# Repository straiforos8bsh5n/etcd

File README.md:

# Ch55xduino: Small Devices Arduino for ch55x devices

**Getting started on the Ch55x the easy way. Forked from Sduino project, also based on 
ch554_sdcc project**

Ch55xduino is an Arduino-like programming API for the CH55X, a family of low-cost MCS51 USB MCU. The project tries to remove the difficulty of setting up a compiling environment. Users can simply write code in Arduino IDE and hit one button to flash the chip to get code running. No configuration or guesswork needed. 

CH551, CH552, CH554, may be the lowest part count system that works with Arduino. The minimal system only requires one chip, 2 decoupling capacitors, and one optional pull-up resistor. These features made it ideal for DIY projects. 

At this moment the project is still working-in-progress. Support most Arduino functions (Except pulse, shift, tone). Refer to examples in this repo for more info.

## Installation

Automatic IDE integration is supported via the
Arduino Boards Manager. This is the recommanded way of installation now. 

Start the Arduino-IDE. In *File->Preferences*, *Settings* tab, enter

> https://raw.githubusercontent.com/DeqingSun/ch55xduino/ch55xduino/package_ch55xduino_mcs51_index.json

as an *Additional Boards Manager URL*.

* Open *Tools->Board:...->Boards Manager*
* Find Ch55xduino by typing 'ch' into the search line
* Click on the list entry
* Click on *Install*.

Now you should find a new entry *CH55x Boards* in the list at
*Tools->Board:...*

* Choose *CH552 Board* from the list
* open the standard Blink example from *File->Examples->01. Basics->Blink*
* Change pin number in Blink example. For example, if you have LED on P3_0, you will write pin 30.
* compile it by hitting *Verify*
* If your board is never used with ch55xduino before, you need to make the ch55x chip enter bootloader mode. You need to disconnect USB and unpower ch55x, connect the pull-up resistor on D+ line (generally a 10K resistor between D+ and 5V, controlled by a push-button or adjacent pads). Then you connect USB. and hit *Upload*. Also, a blank new chip will enter the bootloader automatically.
* If you have used ch55xduino once and your code doesn't crash the USB subsystem, you can simply press *Upload*. Arduino and the firmware will kick the chip into the bootloader automatically.

### Installation without Github access

If you can not access github directly, use this link to a proxy instead.

> https://gh-proxy.deqing.workers.dev/raw.githubusercontent.com/DeqingSun/ch55xduino/playground/mirror/package_ch55xduino_mcs51_proxy_index.json

### USB and Serial upload

Ch55xduino supports both USB and Serial upload methods. If the USB port of the CH55x chip is connected to a host computer, the USB method is recommended.

It is also possible to upload via serial on UART1 of CH55x chips (except CH551). To set CH55x into bootloader mode automatically, you can connect RTS or DTR of a serial adaptor to an interrupt pin of CH55x with a capacitor, and add bootloader jumping code in the interrupt handler.

If you want to leave the bootloader, you may send the following bytes at 57600 baud. ```57 AB A2 01 00 01 A4```  

### Driver for windows

Since 0.0.10, if your Windows automatically installed the driver from wch.cn for the bootloader (4348,55E0), that is fine. The current upload tool can use the default CH375 driver and co-exist with the official [WCHISPTool](http://www.wch.cn/downloads/WCHISPTool_Setup_exe.html).

If you need to use WinUSB or libusb-win32, the tool will still work.

You can use USB Serial (CDC) driver for the default CDC USB stack (1209,C550). Use [Zadig](https://zadig.akeo.ie/) to install the driver if it did not install automatically.

If you tried to emulate another type of USB device without changing the PID/VID, you may need to uninstall the device before installing a new driver.

### Permission for Linux

By default, Linux will not expose enough permission for Arduino to upload the code with the USB bootloader. Copy ```99-ch55xbl.rules``` in this repo to ```/etc/udev/rules.d/``` and restart your computer. Otherwise, the upload tool may not find the bootloader device.

## Reference board

There is a small CH552 breakout board design in the "pcb" folder. When fabricated with 1.6mm board thickness, some USB receptacle may be too loose for the PCB. Just add some tape behind the USB connector to increase the thickness.

The button footprint was designed for 6mm buttons, but 5mm one works too.

## Difference to regular Arduino

### Pin names:

Regular Arduino uses continuous numbers to code pins on AVR chips. In my opinion, it makes more sense since AVR uses letters as a port name. But MCS51 core uses numbers as port names. So CH55xduino's pins using the following rule. 

```PortNumber*10+PinNumber```

For example, P1.1 is 11, P3.2 is 32.

### Analog input:

CH552 has an 8-bit, 4 channel analog-to-digital converter on pin P1.1, P1.4, P1.5, and P3.2. So the input range is 0~255, not 1023.

By default, all pins on the MCS51 microcontrollers have internal pull-up resistors enabled. You may need to use ```pinMode``` to set the pin to ```INPUT``` to disable the pull-up resistor. 

There is no Analog Pin definition such as A0. Just use 11, 14, 15, or 32 for their analog input feature.

### No polymorph functions:

There is no free C++ compiler for MCS51 chip, we can not use polymorph functions. However, since commit 13402 of SDCC, the generic selection is functional. Ch55xduino supports generic selection since 0.0.11.

If you are using a version higher than 0.0.11, the print function can choose a function according to the parameter's type. 

For example. If you want to print to the USB-CDC virtual serial port, you can do:

```
USBSerial_print(val);	//val: the value to print - any data type
USBSerial_print(val, format)	//specifies the number base (for integral data types) or number of decimal places (for floating point types)
USBSerial_print(charPointer, length)	//specifies the string length to be printed 
```

It is also possible to do ``` USBSerial_println ```. If you want to print to Serial0 or Serial1, just use ``` Serial0_print ``` or ``` Serial1_print ```.

Please note if you pass a character in single quotes, such as ```USBSerial_print(',');```, you will get ```44```. Because that char got promoted to integer type. You need to either use ```USBSerial_print((char)',');``` or ```USBSerial_print(",");```.

They are defined in ```genericPrintSelection.h```.

### Memory model:

Unlike most modern architectures including AVR, MCS51 has 2 RAM regions, internal data memory, and external data memory. For CH552, the internal one is only 256 bytes, and the external one is 1024 bytes.

CH55xduino uses the default Small Model for SDCC memory models. The small memory model will allocate all variables in internal, directly addressable RAM by default. Variables stored in external RAM must be declared with the ```xdata``` or ```far``` keyword. 

CH55xduino also put the stack in internal RAM. So there isn't much space left for variables. If your variable doesn't need fast access, use ```__xdata``` when you declare it.  

For example, if you are trying to allocate a lot of space in internal RAM.

```uint8_t testArr[128];```

You will trigger an error. ```?ASlink-Error-Could not get 130 consecutive bytes in internal RAM for area DSEG.``` This can be avoided by using

```__xdata uint8_t testArr[128];```

For the default Arduino setting, 148 bytes are reserved for USB endpoints. There will be 876 bytes usable for external RAM.

You can see the memory mapping by opening the map and mem file generated along with the hex file.

#### Common Pitfalls when Using SDCC

Note that when some function is called from an interrupt service routine it should be preceded by a #pragma NOOVERLAY (if it is not reentrant) . A special note here, int (16 bit) and long (32 bit) integer division, multiplication & modulus operations are implemented using external support routines developed in ANSI-C, if an interrupt service routine needs to do any of these operations then the support routines (as mentioned in a following section) will have to recompiled using the --stack-auto option and the source file will need to be compiled using the --int-long-rent compiler option. [src](http://fivedots.coe.psu.ac.th/~cj/masd/resources/sdcc-doc/SDCCUdoc-11.html)

With SDCC, interrupt service routine function prototypes must be placed in the file that contains main ( ) in order for an vector for the interrupt to be placed in the the interrupt vector space.  It's acceptable to place the function prototype in a header file as long as the header file is included in the file that contains main ( ).  SDCC will not generate any warnings or errors if this is not done, but the vector will not be in place so the ISR will not be executed when the interrupt occurs. [src](https://www.silabs.com/community/mcu/8-bit/knowledge-base.entry.html/2007/11/16/common_pitfalls_when-E7zi)

### Reset Pins

Unlike AVR chips, CH55x will reset when the RST pin is High. The reset pin may be configured as an input pin. But such configuration requires modification of Configuration Information byte, which require an external tool to do so.

## Known issues

.

## Included libraries

Most parts of the Arduino core system and some Arduino libraries are already ported to C-syntax. The resulting API is still very close to the C++ version and porting an existing application is not hard. Refer to the examples that come with the libraries.

#### Communication

* SPI: Real hardware-SPI up to 12MHz.

* SoftI2C: Bit-Bang I2C on any 2 pins.

* WS2812: Bit-Bang WS2812 on any pin. Note some compatible LEDs have different timing and some tweak may be needed. 

#### Sensors

* TouchKey: Internal 6-channel capacitive touch module wrapper with an adaptive baseline algorithm.

## Compatibility with the Arduino world

Since there is no free C++ compiler for the MCS51, it is impossible to do a
full 1:1 port of the whole enviroment as is has been done for the STM32 and
the ESP8266.

This is not a drop-in replacement for an AVR, but thanks to some C
preprocessor magic the programming API is still very, very similar and it is
often enough to just move over the opening bracket of the class
instanciation statement and to replace the dot in a method call for an
underscore. Check the [migration
guide](https://tenbaht.github.io/sduino/api/migration/) for an overview.

## Supported Systems:

Arduino IDE versions 1.8.12 are tested, but
most versions >=1.6.6 should work.

* Windows: Tested on Windows 7 and XP.

* MacOS: Tested on 10.14.

* Linux: Tested on Ubuntu 20.04 LTS.

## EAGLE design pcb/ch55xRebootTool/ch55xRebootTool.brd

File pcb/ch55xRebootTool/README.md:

# ch55xRebootTool

ch55xRebootTool is a hardware tool to reset a WCH chip target into the bootloader without touching the board with your finger. It solves 2 problems: 

1. Some chips can not jump to bootloader from user code.

2. When you are developing the USB host code, the USB port will be occupied by a device.

## How to use the tool

### Basic usage

Connect 2 micro USB cables from the computer to the 2 micro USB ports on the left. The upper one is connected to the target, and the lower one is to send commands to the controller on board.

The left MicroUSB port and the USB A port next to it are connected. The target can be plugged into either port.

If your target chip needs to pull down a pin to enter the bootloader, connect that pin to the P1.6 on the board. If the target uses D+, no connection is needed.

Open the ch55xRebootTool serial port @ 1200 rate and it will kick target into the bootloader.

### Use the serial adapter

This board can also be used as a serial adapter. Just use the 3-pin header on the right. Note the board can not work at the 1200 rate or higher than 115200. 

### Use a USB device for host code development

Plug the device on the USB port on the right side of the top. When the P1.7 on the board gets pulled down. The board will supply power to the device, and switch the target from the computer to the device. You may use a pin on the target to do the control

Note the target will switch back to the computer in bootloader mode.

## Enter the bootloader

Most WCH chips can upload firmware via USB. However, the chip must enter the bootloader to upload the firmware. Generally, there are 2 ways to enter bootloader:

1. Pull a specific pin to GND or D+ to VCC, depending on your settings in the configuration byte. Then power the chip.

2. Jump into the bootloader within the user code. But this does not work for chips such as CH549.

If you already played with the CH55xduino on a CH55x chip, you may not feel the pain. Because when you upload the code, the Arduino environment will open the virtual serial port on the CH55x chip at a 1200 baud rate. The CH55xduino firmware will jump to the bootloader automatically and receive the code from the computer. The user experience is just pressing a button on your computer and everything gets ready. 

But if the firmware is not working properly or you are using chips like CH549, the chip won't enter the bootloader automatically. You may need to unplug the USB cable, hold a button and plug the USB cable back, that is a pain when you repeat the process over and over again.

Instead of doing it manually, the ch55xRebootTool will act as a serial adapter. When you open the serial port at a 1200 baud rate, the tool will disconnect the power from the target chip using a PMOS, connect a 10K resistor to D+, and pulldown the pin P1.6, before restoring the power cycle. Basically, the ch55xRebootTool does the power cycle and pulls the pin for you. 

## Use a USB device

When developing the host code, you may need to switch the target back and forth between the computer and the device. This tool does it automatically for you. You just need to pull the Pin 1.7 low to connect the device. When it is released, the target will be connected back to the computer. 

When I design the board. I wish the target can send a reset command on the USB bus, and the controller knows when the target left the bootloader, and can switch to the device automatically. But I have not got it working so far.

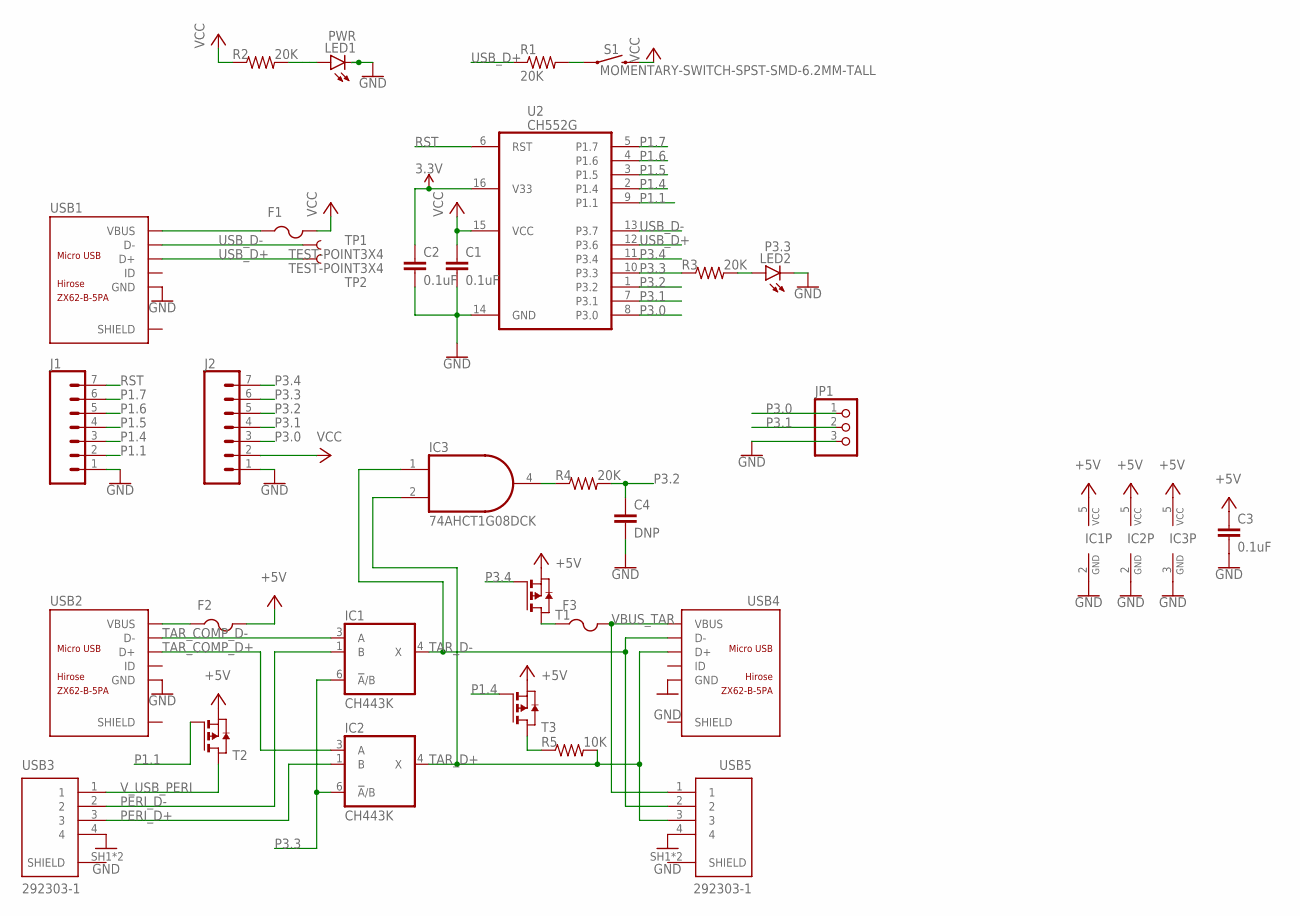
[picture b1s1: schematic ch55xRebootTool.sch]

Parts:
C1, C2, C3: 0.1uF; C0805K; LCSC C16834
C4: DNP; C0805K
F1, F2, F3: PTCFUSE-1206; R1206; LCSC C151162
IC1, IC2: CH443K; DCK_R-PDSO-G6; LCSC C125185
IC3: 74AHCT1G08DCK; SC70-5; LCSC C12493
J1, J2: CONN_07NO_SILK; 1X07_NO_SILK
JP1: PINHD-1X3; 1X03
LED1: PWR; GHI-BASICCOMPONENTS_0805-LED
LED2: P3.3; GHI-BASICCOMPONENTS_0805-LED
R1, R2, R3, R4: 20K; R0805
R5: 10K; R0805
S1: MOMENTARY-SWITCH-SPST-SMD-6.2MM-TALL; TACTILE_SWITCH_SMD_6.2MM_TALL
T1, T2, T3: PMOSSOT23; SOT-23
TP1, TP2: TEST-POINT3X4; PAD.03X.04
U2: CH552G; MY_IC_SO16; LCSC C111292
USB1, USB2, USB4: ZX62-B-5PA; MICRO-USB5+6P-SMD-0.65-AB; LCSC C10418
USB3, USB5: 292303-1; LCSC C2345

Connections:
3.3V: C2.1, U2.16 (V33)
+5V: C3.1, F2.2, IC1.5 (VCC), IC2.5 (VCC), IC3.5 (VCC), T1.2 (S), T2.2 (S), T3.2 (S)
GND: C1.2, C2.2, C3.2, C4.2, IC1.2 (GND), IC2.2 (GND), IC3.3 (GND), J1.1, J2.1, JP1.3, LED1.K, LED2.K, U2.14 (GND), USB1.5 (GND), USB2.5 (GND), USB3.4, USB4.5 (GND), USB5.4
unnamed: R1.2, S1.A2 (1)
unnamed: LED2.A, R3.2
unnamed: LED1.A, R2.2
unnamed: IC3.4 (O), R4.1
unnamed: F3.1, T1.1 (D)
unnamed: R5.1, T3.1 (D)
P1.1: J1.2, T2.3 (G), U2.9 (P1.1)
P1.4: J1.3, T3.3 (G), U2.2 (P1.4)
P1.5: J1.4, U2.3 (P1.5)
P1.6: J1.5, U2.4 (P1.6)
P1.7: J1.6, U2.5 (P1.7)
P3.0: J2.3, JP1.1, U2.8 (P3.0)
P3.1: J2.4, JP1.2, U2.7 (P3.1)
P3.2: C4.1, J2.5, R4.2, U2.1 (P3.2)
P3.3: IC1.6 (!A!/B), IC2.6 (!A!/B), J2.6, R3.1, U2.10 (P3.3)
P3.4: J2.7, T1.3 (G), U2.11 (P3.4)
PERI_D+: IC2.1 (B), USB3.3
PERI_D-: IC1.1 (B), USB3.2
RST: J1.7, U2.6 (RST)
SHIELD: USB3.SH1 (SHIELD), USB3.SH2 (SHIELD), USB5.SH1 (SHIELD), USB5.SH2 (SHIELD)
TAR_COMP_D+: IC2.3 (A), USB2.3 (D+)
TAR_COMP_D-: IC1.3 (A), USB2.2 (D-)
TAR_D+: IC2.4 (X), IC3.2 (I1), R5.2, USB4.3 (D+), USB5.3
TAR_D-: IC1.4 (X), IC3.1 (I0), USB4.2 (D-), USB5.2
USB_D+: R1.1, TP2.P$1, U2.12 (P3.6), USB1.3 (D+)
USB_D-: TP1.P$1, U2.13 (P3.7), USB1.2 (D-)
VBUS: F1.1, USB1.1 (VBUS)
VBUS_COMP: F2.1, USB2.1 (VBUS)
VBUS_TAR: F3.2, USB4.1 (VBUS), USB5.1
VCC: C1.1, F1.2, J2.2, R2.1, S1.B2 (2), U2.15 (VCC)
V_USB_PERI: T2.1 (D), USB3.1

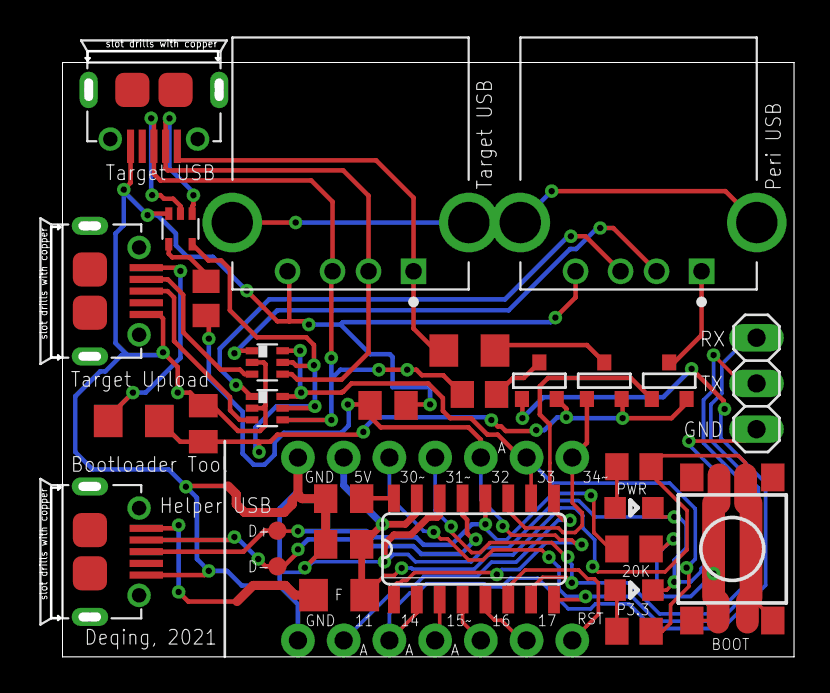
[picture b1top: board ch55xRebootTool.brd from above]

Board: 2 copper layers, 41.3 x 33.7 mm, 32 parts (0 on the bottom side), 34 nets.

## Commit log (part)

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2024-06-06 inital commit
2024-06-15 Implemented SWIM and CLI interface
2024-06-17 readme changed
2024-06-26 Multiple programmers are now supported
2024-07-05 Added parts DB
2024-07-13 Moved out_usleep to struct programmer_s
2024-07-23 Moved out_msg_size to struct programmer_s
2024-07-29 Detach device from kernel module
2024-08-05 test_unit_ready & related utility functions
2024-08-16 Use little-endian for data length
2024-08-22 Implemented stlinkv1 open
2024-08-25 Test stlinkv1 for being initialized
2024-08-26 Fixed stack smashing
2024-09-01 Implemented stlink_swim_read_range
2024-09-03 Implemented stlink_init_io
2024-09-15 Implemented stlink_prepare_transfer
2024-09-25 Got rid from segmentation fault when -b > 16
2024-09-29 Implemented stlink_swim_write_range
2024-10-03 Handle writing buffer overflow
2024-10-12 Limit write tries
2024-10-23 Implemented stlink_finish_session
2024-10-26 No need to write in DM_CSR2
2024-10-28 Implemented a block reading cycle
2024-10-31 Wrapped debug in DEBUG_PRINT(..)
2024-11-04 Fixed memory sizes
2024-11-11 Implemented stlink_swim_write_block
2024-11-16 Implemented stlink_swim_wait
2024-11-17 stlink_swim_get_status now respects the previous CBW
2024-11-22 Implemented writing by 128-byte blocks
2024-11-23 Padding blocks with '\0'
2024-12-03 Added make install
2024-12-04 Reset MCU core after writing completes
2024-12-07 add support for stm8s103
2024-12-20 Moved src/* to root
2024-12-21 Refactoring of stlinkv2.c
    TODO: compare stlink.c and stlinkv2.c and remove redudancies
2025-01-01 removed programmer_t.out_usleep
2025-01-07 Fixed stlinkv2 writing that was broken with #001df0ea
2025-01-16 Update Makefile
2025-01-24 Missing stlinkv2.h
2025-02-03 -f option deprecated
2025-02-14 Intel HEX support
2025-02-17 Moved hard-coded registers to stm8.c
2025-02-26 Removed internal methods from stlink.h and stlinkv2.h
2025-03-02 stlink2_finish_session()
2025-03-08 stlinkv2 doesn't resets after writing (broken by #69563454d3)
2025-03-09 STM8S208 support
2025-03-21 print_help_and_exit() update
2025-03-24 build(deps): bump github.com/prometheus/procfs from 0.15.1 to 0.16.0
    Bumps [github.com/prometheus/procfs](https://github.com/prometheus/procfs) from 0.15.1 to 0.16.0.
    - [Release notes](https://github.com/prometheus/procfs/releases)
    - [Commits](https://github.com/prometheus/procfs/compare/v0.15.1...v0.16.0)
    ---
    updated-dependencies:
    - dependency-name: github.com/prometheus/procfs
2025-03-28 Write 0x82 instead of 0x00 in stlink2_wait_until_transfer_completes()
2025-04-04 Fixed stlinkv2 writing (broken by #b754a32050)
2025-04-12 Changed condition in stlink2_wait_until_transfer_completes()
2025-04-13 fix issue3 stm8s105 etc has 128-bytes memory blocks instead 64-bytes on stm8s003 etc. Added `flash_block_size` to device description
2025-04-25 fix make clean
2025-04-29 Flash write fixes stm8s105 over both stlink v1/v2 now work stm8l152 over both stlink v1/v2 now work
2025-05-11 Fixed a segfault when file_name doesn't contains dot
2025-05-22 Patch from Philipp Klaus Krause
    1. Check that file exists
    2. Display file type when writing (binary or Intel hex)
2025-05-23 read/write flash/eeprom work. stm8s003 tested
2025-05-24 Verify action
2025-06-01 Write flash stm8s003 over stlink v1. Test table
2025-06-13 ignores
2025-06-27 support table
2025-07-08 support table fix
2025-07-17 Add [-b bytes] to usage output.
2025-07-25 This builds stm8flash on MacOS X (10.9.5)
2025-08-12 Patch that fixes Mac OS X build from Philipp Klaus Krause
2025-08-23 Claim interface on OS X.
2025-08-28 Fix MacOSX build
2025-09-05 adding flash support for stm8l051f3
2025-09-09 Added support for stm8s005k6
2025-09-15 Added support to write OPT bytes
2025-09-30 Correct check for max OPT size (for 0x80 for high density devices)
2025-10-07 Inferring exact option size from device size
2025-10-15 Added debug string
2025-10-22 Restored comment
2025-10-29 Using correct start address too
2025-11-07 Inferring correct option size from device size
2025-11-26 Added support for STM8L101F1 & STM8L101F2, fixed mix-indent
2025-12-06 More verbose usage information, list supported devices
2025-12-13 Add support for all current STM8S devices
2025-12-18 make part table const
2025-12-23 Support more STM8L devices
2025-12-25 Add support for some STM8A parts
2026-01-02 Add support for STLUX
2026-01-10 Add support for STNRG
2026-01-19 Add GPLv2 text
2026-01-25 STM8S103F3/STM8S103K3 test result
2026-02-04 Tested on STM8A-Discovery
2026-02-16 Add support for all current STM8AF parts
2026-02-20 Support more STM8AL parts
2026-02-28 Support more STM8L parts
2026-03-07 Support STM8L101 (except for eeprom)
2026-03-17 STM8T support
2026-03-27 Tested on STM8L101-EVAL
2026-04-02 Fix typo in README
2026-04-13 Further testing results
2026-04-15 Add windows executable into gitignore list
2026-04-18 Intentional help invocation is not an error
2026-04-27 Fix bug on Raspberry pi
    This fixes a bug where the option parser does not recognize the end of the array.
2026-05-07 fixes to allows compiling under windows (mingw-w64-i686)
2026-05-09 Adding intel hex output format
2026-05-21 Fix makefile for Darwin platform
2026-06-05 Clean up and improve makefile, including not failing if the user passes their own CFLAGS.
2026-06-16 Add compile-time option to build with quieter libusb debug level.
2026-06-22 Accept .hex as a valid extension for an intel hex file too, not just .ihx

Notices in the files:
parts and their libraries:
SparkFun-Connectors: Licensing: Creative Commons ShareAlike 4.0 International - https://creativecommons.org/licenses/by-sa/4.0
